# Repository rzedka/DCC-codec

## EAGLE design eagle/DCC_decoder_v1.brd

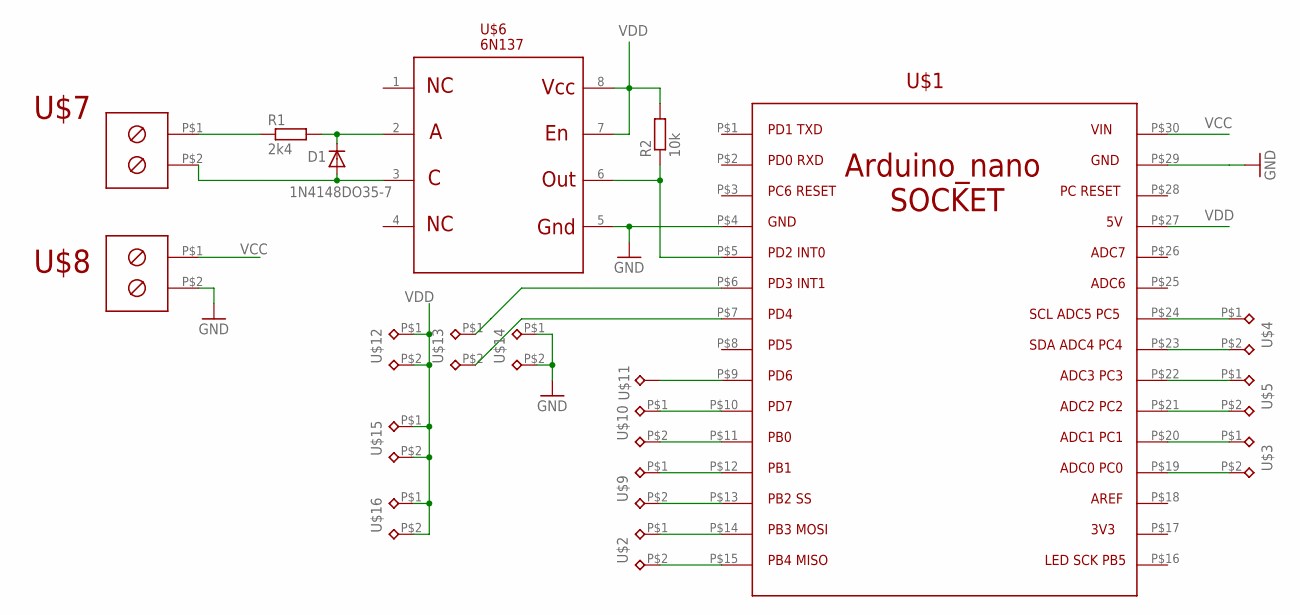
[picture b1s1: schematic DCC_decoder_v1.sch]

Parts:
D1: 1N4148DO35-7; DO35-7
R1: 2k4; 0207/2V
R2: 10k; 0207/2V
U$1: ARD_NANO_SOCKET
U$2, U$3, U$4, U$5, U$9, U$10, U$12, U$13, U$14, U$15, U$16: TP_2; TESTPAD_2
U$6: 6N137; DIL-8
U$7, U$8: CON_2PIN
U$11: TESTPAD

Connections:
GND: U$1.P$4, U$1.P$29, U$6.5, U$8.P$2, U$14.P$1, U$14.P$2
unnamed: D1.C, R1.2, U$6.2
unnamed: D1.A, U$6.3, U$7.P$2
unnamed: R1.1, U$7.P$1
unnamed: U$1.P$15, U$2.P$2
unnamed: R2.1, U$1.P$5, U$6.6
unnamed: U$1.P$14, U$2.P$1
unnamed: U$1.P$13, U$9.P$2
unnamed: U$1.P$12, U$9.P$1
unnamed: U$1.P$11, U$10.P$2
unnamed: U$1.P$10, U$10.P$1
unnamed: U$1.P$9, U$11.P$1
unnamed: U$1.P$7, U$13.P$2
unnamed: U$1.P$6, U$13.P$1
unnamed: U$1.P$19, U$3.P$2
unnamed: U$1.P$20, U$3.P$1
unnamed: U$1.P$21, U$5.P$2
unnamed: U$1.P$22, U$5.P$1
unnamed: U$1.P$23, U$4.P$2
unnamed: U$1.P$24, U$4.P$1
VCC: U$1.P$30, U$8.P$1
VDD: R2.2, U$1.P$27, U$6.7, U$6.8, U$12.P$1, U$12.P$2, U$15.P$1, U$15.P$2, U$16.P$1, U$16.P$2

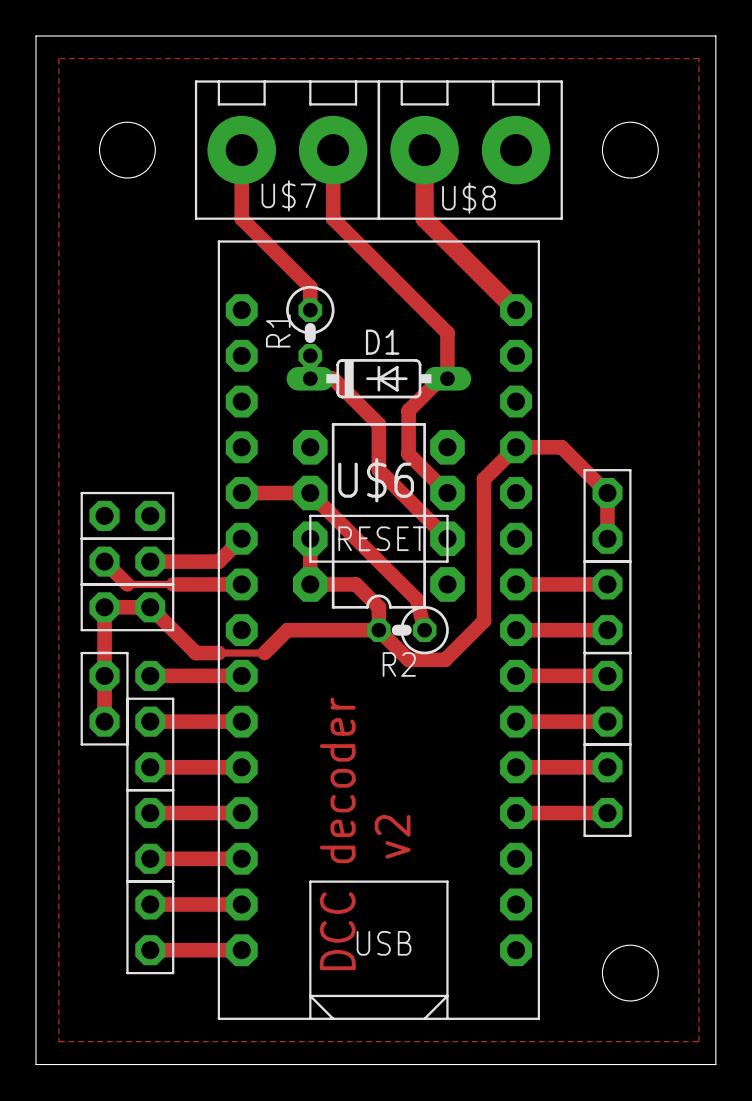
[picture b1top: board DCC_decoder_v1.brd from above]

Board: 2 copper layers, 37.8 x 57.1 mm, 19 parts (0 on the bottom side), 22 nets.

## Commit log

2023-01-19 Adding sources and headers
2023-01-19 adding codeblocks project and documents
2023-02-18 DCC decoder board v2
2023-02-18 DCC decoder board v2 - minor changes
